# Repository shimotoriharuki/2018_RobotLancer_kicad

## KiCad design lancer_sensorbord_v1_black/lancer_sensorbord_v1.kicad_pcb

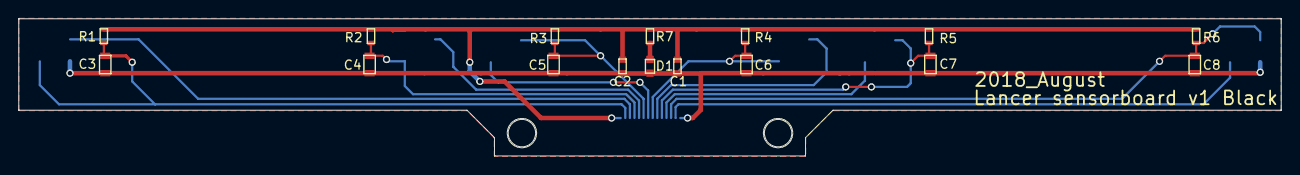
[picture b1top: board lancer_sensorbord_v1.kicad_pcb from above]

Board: 2 copper layers, 138.0 x 15.0 mm, 23 parts (0 on the bottom side), 15 nets.

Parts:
C1, C2: 0.1u; C_1608_HandSolderring_1000pF
C3, C4, C5, C6, C7, C8: 1000p; C_2012_HandSolderring_0.1u
D1: LED_ALT; LED 1608
LineSensor: CN-FFC-SMT2(CN-FFC(0.5)14PD)
PI1, PI2, PI3, PI4, PI5, PI6: GP2S700HCP
R1, R2, R3, R4, R5, R6: 100k; R_1608_HandSoldering
R7: 330; R_1608_HandSoldering

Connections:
+3V3: C1.1, C2.1, LineSensor.1, R1.1, R2.1, R3.1, R4.1, R5.1, R6.1, R7.1
ANALOG_SEN1: C3.1, LineSensor.2, PI1.2, R1.2
ANALOG_SEN2: C4.1, LineSensor.4, PI2.2, R2.2
ANALOG_SEN3: C5.1, LineSensor.6, PI3.2, R3.2
ANALOG_SEN4: C6.1, LineSensor.8, PI4.2, R4.2
ANALOG_SEN5: C7.1, LineSensor.10, PI5.2, R5.2
ANALOG_SEN6: C8.1, LineSensor.12, PI6.2, R6.2
GND: C1.2, C2.2, C3.2, C4.2, C5.2, C6.2, C7.2, C8.2, D1.1, LineSensor.14, PI1.1, PI1.3, PI2.1, PI2.3, PI3.1, PI3.3, PI4.1, PI4.3, PI5.1, PI5.3, PI6.1, PI6.3
unnamed: D1.2, R7.2
VR1: LineSensor.3, PI1.4
VR2: LineSensor.5, PI2.4
VR3: LineSensor.7, PI3.4
VR4: LineSensor.9, PI4.4
VR5: LineSensor.11, PI5.4
VR6: LineSensor.13, PI6.4
